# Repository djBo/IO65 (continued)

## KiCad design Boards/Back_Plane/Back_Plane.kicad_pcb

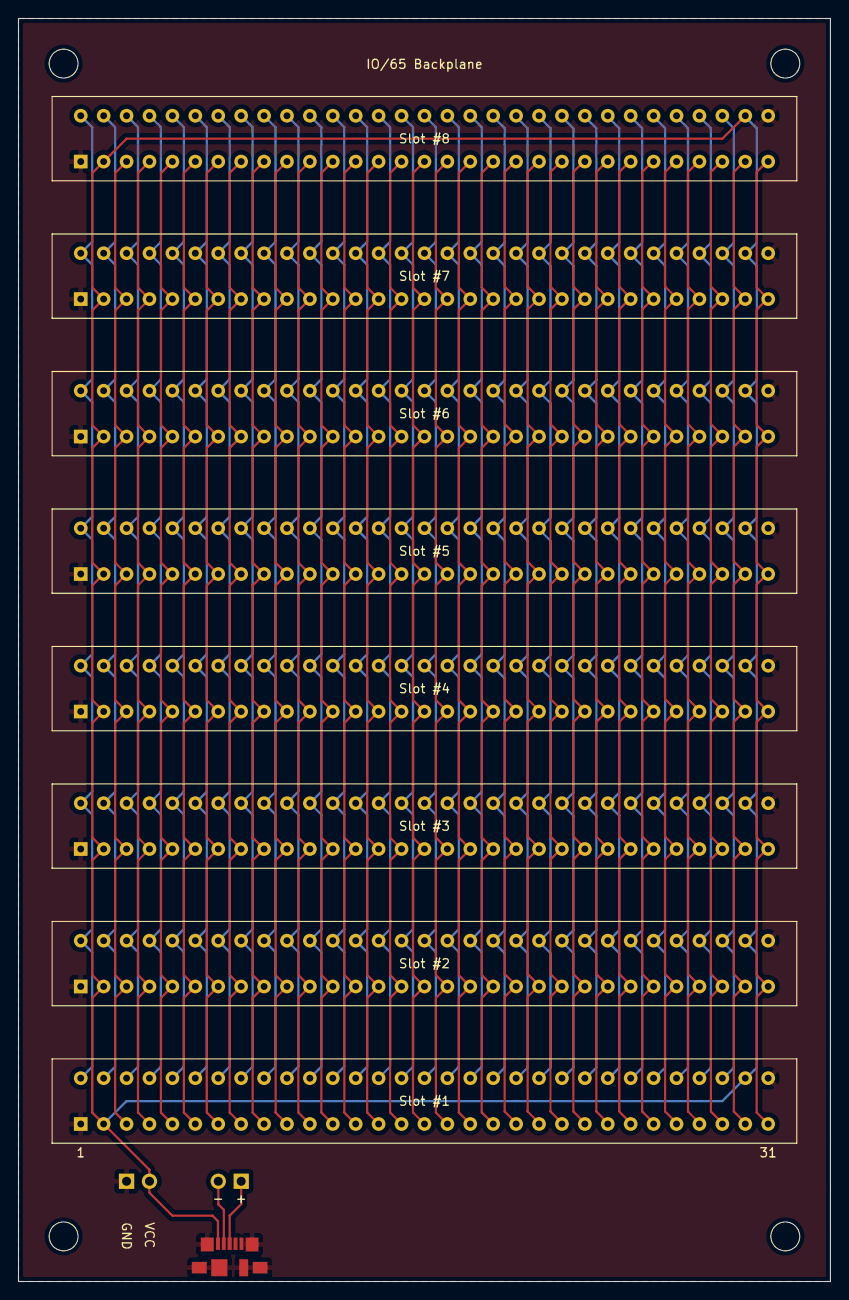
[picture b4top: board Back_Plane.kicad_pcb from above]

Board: 2 copper layers, 90.0 x 140.0 mm, 11 parts (0 on the bottom side), 62 nets.

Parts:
DATA1: Conn_01x02_Male; PinHeader_1x02_P2.54mm_Vertical
PWR1: Conn_01x02_Male; PinHeader_1x02_P2.54mm_Horizontal
Slot #1, Slot #2, Slot #3, Slot #4, Slot #5, Slot #6, Slot #7, Slot #8: Edge Connector; 6-5530843-5
USB1: USB_B_Micro; USB_Micro-B_Molex_47346-0001

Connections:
A0: Slot #1.47, Slot #2.47, Slot #3.47, Slot #4.47, Slot #5.47, Slot #6.47, Slot #7.47, Slot #8.47
A1: Slot #1.46, Slot #2.46, Slot #3.46, Slot #4.46, Slot #5.46, Slot #6.46, Slot #7.46, Slot #8.46
A2: Slot #1.45, Slot #2.45, Slot #3.45, Slot #4.45, Slot #5.45, Slot #6.45, Slot #7.45, Slot #8.45
A3: Slot #1.44, Slot #2.44, Slot #3.44, Slot #4.44, Slot #5.44, Slot #6.44, Slot #7.44, Slot #8.44
A4: Slot #1.43, Slot #2.43, Slot #3.43, Slot #4.43, Slot #5.43, Slot #6.43, Slot #7.43, Slot #8.43
A5: Slot #1.42, Slot #2.42, Slot #3.42, Slot #4.42, Slot #5.42, Slot #6.42, Slot #7.42, Slot #8.42
A6: Slot #1.41, Slot #2.41, Slot #3.41, Slot #4.41, Slot #5.41, Slot #6.41, Slot #7.41, Slot #8.41
A7: Slot #1.40, Slot #2.40, Slot #3.40, Slot #4.40, Slot #5.40, Slot #6.40, Slot #7.40, Slot #8.40
A8: Slot #1.39, Slot #2.39, Slot #3.39, Slot #4.39, Slot #5.39, Slot #6.39, Slot #7.39, Slot #8.39
A9: Slot #1.38, Slot #2.38, Slot #3.38, Slot #4.38, Slot #5.38, Slot #6.38, Slot #7.38, Slot #8.38
A10: Slot #1.37, Slot #2.37, Slot #3.37, Slot #4.37, Slot #5.37, Slot #6.37, Slot #7.37, Slot #8.37
A11: Slot #1.36, Slot #2.36, Slot #3.36, Slot #4.36, Slot #5.36, Slot #6.36, Slot #7.36, Slot #8.36
A12: Slot #1.35, Slot #2.35, Slot #3.35, Slot #4.35, Slot #5.35, Slot #6.35, Slot #7.35, Slot #8.35
A13: Slot #1.34, Slot #2.34, Slot #3.34, Slot #4.34, Slot #5.34, Slot #6.34, Slot #7.34, Slot #8.34
A14: Slot #1.33, Slot #2.33, Slot #3.33, Slot #4.33, Slot #5.33, Slot #6.33, Slot #7.33, Slot #8.33
A15: Slot #1.32, Slot #2.32, Slot #3.32, Slot #4.32, Slot #5.32, Slot #6.32, Slot #7.32, Slot #8.32
CA1: Slot #1.60, Slot #2.60, Slot #3.60, Slot #4.60, Slot #5.60, Slot #6.60, Slot #7.60, Slot #8.60
CA2: Slot #1.59, Slot #2.59, Slot #3.59, Slot #4.59, Slot #5.59, Slot #6.59, Slot #7.59, Slot #8.59
CS0: Slot #1.22, Slot #2.22, Slot #3.22, Slot #4.22, Slot #5.22, Slot #6.22, Slot #7.22, Slot #8.22
CS1: Slot #1.23, Slot #2.23, Slot #3.23, Slot #4.23, Slot #5.23, Slot #6.23, Slot #7.23, Slot #8.23
CS2: Slot #1.24, Slot #2.24, Slot #3.24, Slot #4.24, Slot #5.24, Slot #6.24, Slot #7.24, Slot #8.24
CS3: Slot #1.25, Slot #2.25, Slot #3.25, Slot #4.25, Slot #5.25, Slot #6.25, Slot #7.25, Slot #8.25
CS4: Slot #1.26, Slot #2.26, Slot #3.26, Slot #4.26, Slot #5.26, Slot #6.26, Slot #7.26, Slot #8.26
CS5: Slot #1.27, Slot #2.27, Slot #3.27, Slot #4.27, Slot #5.27, Slot #6.27, Slot #7.27, Slot #8.27
CS6: Slot #1.28, Slot #2.28, Slot #3.28, Slot #4.28, Slot #5.28, Slot #6.28, Slot #7.28, Slot #8.28
CS7: Slot #1.29, Slot #2.29, Slot #3.29, Slot #4.29, Slot #5.29, Slot #6.29, Slot #7.29, Slot #8.29
CS8: Slot #1.30, Slot #2.30, Slot #3.30, Slot #4.30, Slot #5.30, Slot #6.30, Slot #7.30, Slot #8.30
CS9: Slot #1.31, Slot #2.31, Slot #3.31, Slot #4.31, Slot #5.31, Slot #6.31, Slot #7.31, Slot #8.31
D0: Slot #1.9, Slot #2.9, Slot #3.9, Slot #4.9, Slot #5.9, Slot #6.9, Slot #7.9, Slot #8.9
D1: Slot #1.10, Slot #2.10, Slot #3.10, Slot #4.10, Slot #5.10, Slot #6.10, Slot #7.10, Slot #8.10
D2: Slot #1.11, Slot #2.11, Slot #3.11, Slot #4.11, Slot #5.11, Slot #6.11, Slot #7.11, Slot #8.11
D3: Slot #1.12, Slot #2.12, Slot #3.12, Slot #4.12, Slot #5.12, Slot #6.12, Slot #7.12, Slot #8.12
D4: Slot #1.13, Slot #2.13, Slot #3.13, Slot #4.13, Slot #5.13, Slot #6.13, Slot #7.13, Slot #8.13
D5: Slot #1.14, Slot #2.14, Slot #3.14, Slot #4.14, Slot #5.14, Slot #6.14, Slot #7.14, Slot #8.14
D6: Slot #1.15, Slot #2.15, Slot #3.15, Slot #4.15, Slot #5.15, Slot #6.15, Slot #7.15, Slot #8.15
D7: Slot #1.16, Slot #2.16, Slot #3.16, Slot #4.16, Slot #5.16, Slot #6.16, Slot #7.16, Slot #8.16
E1: Slot #1.17, Slot #2.17, Slot #3.17, Slot #4.17, Slot #5.17, Slot #6.17, Slot #7.17, Slot #8.17
E2: Slot #1.48, Slot #2.48, Slot #3.48, Slot #4.48, Slot #5.48, Slot #6.48, Slot #7.48, Slot #8.48
GND: PWR1.1, Slot #1.1, Slot #1.62, Slot #2.1, Slot #2.62, Slot #3.1, Slot #3.62, Slot #4.1, Slot #4.62, Slot #5.1, Slot #5.62, Slot #6.1, Slot #6.62, Slot #7.1, Slot #7.62, Slot #8.1, Slot #8.62, USB1.5 (GND), USB1.6 (Shield)
unnamed: DATA1.1, USB1.3 (D+)
unnamed: DATA1.2, USB1.2 (D-)
PA0: Slot #1.58, Slot #2.58, Slot #3.58, Slot #4.58, Slot #5.58, Slot #6.58, Slot #7.58, Slot #8.58
PA1: Slot #1.57, Slot #2.57, Slot #3.57, Slot #4.57, Slot #5.57, Slot #6.57, Slot #7.57, Slot #8.57
PA2: Slot #1.56, Slot #2.56, Slot #3.56, Slot #4.56, Slot #5.56, Slot #6.56, Slot #7.56, Slot #8.56
PA3: Slot #1.55, Slot #2.55, Slot #3.55, Slot #4.55, Slot #5.55, Slot #6.55, Slot #7.55, Slot #8.55
PA4: Slot #1.54, Slot #2.54, Slot #3.54, Slot #4.54, Slot #5.54, Slot #6.54, Slot #7.54, Slot #8.54
PA5: Slot #1.53, Slot #2.53, Slot #3.53, Slot #4.53, Slot #5.53, Slot #6.53, Slot #7.53, Slot #8.53
PA6: Slot #1.52, Slot #2.52, Slot #3.52, Slot #4.52, Slot #5.52, Slot #6.52, Slot #7.52, Slot #8.52
PA7: Slot #1.51, Slot #2.51, Slot #3.51, Slot #4.51, Slot #5.51, Slot #6.51, Slot #7.51, Slot #8.51
RAM: Slot #1.20, Slot #2.20, Slot #3.20, Slot #4.20, Slot #5.20, Slot #6.20, Slot #7.20, Slot #8.20
RDY: Slot #1.6, Slot #2.6, Slot #3.6, Slot #4.6, Slot #5.6, Slot #6.6, Slot #7.6, Slot #8.6
ROM: Slot #1.21, Slot #2.21, Slot #3.21, Slot #4.21, Slot #5.21, Slot #6.21, Slot #7.21, Slot #8.21
R/~W: Slot #1.4, Slot #2.4, Slot #3.4, Slot #4.4, Slot #5.4, Slot #6.4, Slot #7.4, Slot #8.4
SYNC: Slot #1.49, Slot #2.49, Slot #3.49, Slot #4.49, Slot #5.49, Slot #6.49, Slot #7.49, Slot #8.49
VCC: PWR1.2, Slot #1.2, Slot #1.61, Slot #2.2, Slot #2.61, Slot #3.2, Slot #3.61, Slot #4.2, Slot #4.61, Slot #5.2, Slot #5.61, Slot #6.2, Slot #6.61, Slot #7.2, Slot #7.61, Slot #8.2, Slot #8.61, USB1.1 (VBUS)
~IRQ: Slot #1.7, Slot #2.7, Slot #3.7, Slot #4.7, Slot #5.7, Slot #6.7, Slot #7.7, Slot #8.7
~NMI: Slot #1.8, Slot #2.8, Slot #3.8, Slot #4.8, Slot #5.8, Slot #6.8, Slot #7.8, Slot #8.8
~OE: Slot #1.18, Slot #2.18, Slot #3.18, Slot #4.18, Slot #5.18, Slot #6.18, Slot #7.18, Slot #8.18
~RES: Slot #1.5, Slot #2.5, Slot #3.5, Slot #4.5, Slot #5.5, Slot #6.5, Slot #7.5, Slot #8.5
~SO: Slot #1.50, Slot #2.50, Slot #3.50, Slot #4.50, Slot #5.50, Slot #6.50, Slot #7.50, Slot #8.50
~WE: Slot #1.19, Slot #2.19, Slot #3.19, Slot #4.19, Slot #5.19, Slot #6.19, Slot #7.19, Slot #8.19
Φ2: Slot #1.3, Slot #2.3, Slot #3.3, Slot #4.3, Slot #5.3, Slot #6.3, Slot #7.3, Slot #8.3

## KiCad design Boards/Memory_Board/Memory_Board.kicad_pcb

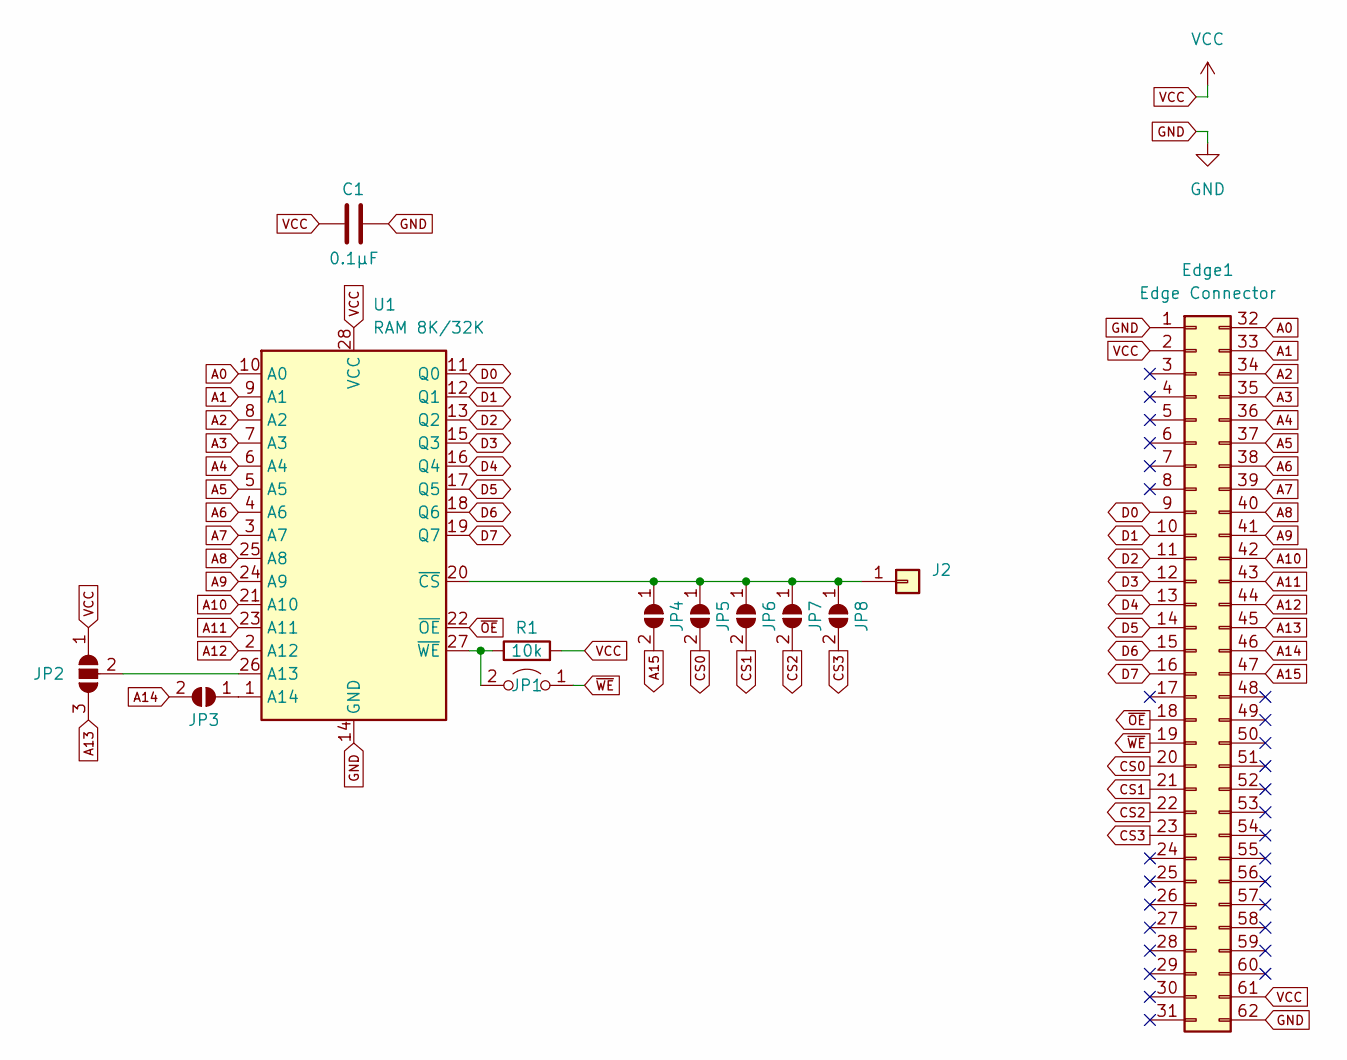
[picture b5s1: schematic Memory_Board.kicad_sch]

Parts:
C1: 0.1µF; C_Disc_D5.0mm_W2.5mm_P2.50mm
Edge1: Edge Connector; BUS_PC_M
J2: Conn_01x01; PinSocket_1x01_P2.54mm_Horizontal
JP1: Jumper_2_Open; PinHeader_1x02_P2.54mm_Horizontal
JP2: SolderJumper_3_Open; SolderJumper-3_P1.3mm_Open_Pad1.0x1.5mm
JP3, JP4, JP5, JP6, JP7, JP8: SolderJumper_2_Open; SolderJumper-2_P1.3mm_Open_Pad1.0x1.5mm
R1: 10k; R_Axial_DIN0207_L6.3mm_D2.5mm_P7.62mm_Horizontal
U1: RAM 8K/32K; DIP-28_W15.24mm_Socket

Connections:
A0: Edge1.32, U1.10 (A0)
A1: Edge1.33, U1.9 (A1)
A2: Edge1.34, U1.8 (A2)
A3: Edge1.35, U1.7 (A3)
A4: Edge1.36, U1.6 (A4)
A5: Edge1.37, U1.5 (A5)
A6: Edge1.38, U1.4 (A6)
A7: Edge1.39, U1.3 (A7)
A8: Edge1.40, U1.25 (A8)
A9: Edge1.41, U1.24 (A9)
A10: Edge1.42, U1.21 (A10)
A11: Edge1.43, U1.23 (A11)
A12: Edge1.44, U1.2 (A12)
A13: Edge1.45, JP2.3 (B)
A14: Edge1.46, JP3.2 (B)
A15: Edge1.47, JP4.2 (B)
CS0: Edge1.20, JP5.2 (B)
CS1: Edge1.21, JP6.2 (B)
CS2: Edge1.22, JP7.2 (B)
CS3: Edge1.23, JP8.2 (B)
D0: Edge1.9, U1.11 (Q0)
D1: Edge1.10, U1.12 (Q1)
D2: Edge1.11, U1.13 (Q2)
D3: Edge1.12, U1.15 (Q3)
D4: Edge1.13, U1.16 (Q4)
D5: Edge1.14, U1.17 (Q5)
D6: Edge1.15, U1.18 (Q6)
D7: Edge1.16, U1.19 (Q7)
GND: C1.2, Edge1.1, Edge1.62, U1.14 (GND)
unnamed: J2.1, JP4.1 (A), JP5.1 (A), JP6.1 (A), JP7.1 (A), JP8.1 (A), U1.20 (~CS)
unnamed 30: JP1.2 (B), R1.1, U1.27 (~WE); also elsewhere on the board
unnamed: JP2.2 (C), U1.26 (A13)
unnamed: JP3.1 (A), U1.1 (A14)
VCC: C1.1, Edge1.2, Edge1.61, JP2.1 (A), R1.2, U1.28 (VCC)
~OE: Edge1.18, U1.22 (~OE)
~WE: Edge1.19, JP1.1 (A); also elsewhere on the board

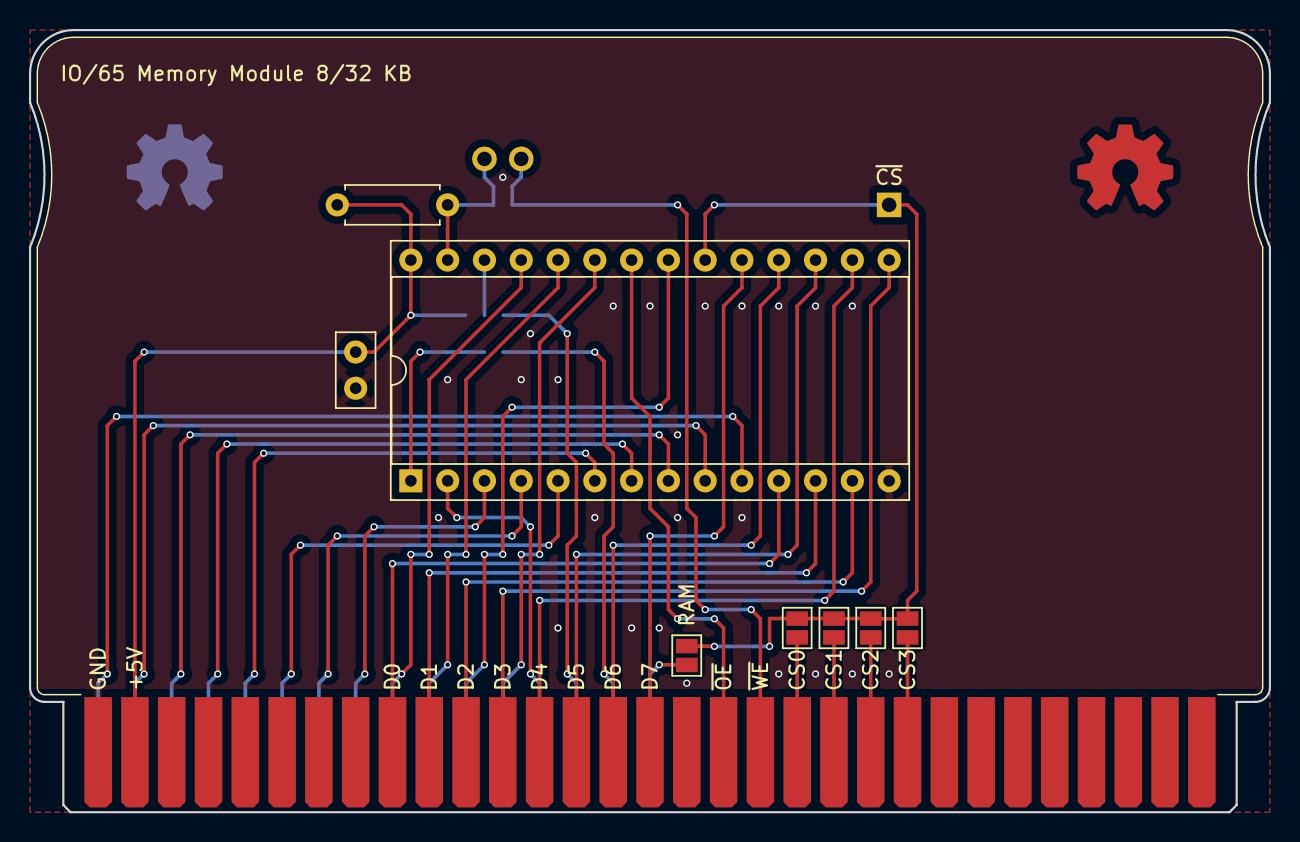
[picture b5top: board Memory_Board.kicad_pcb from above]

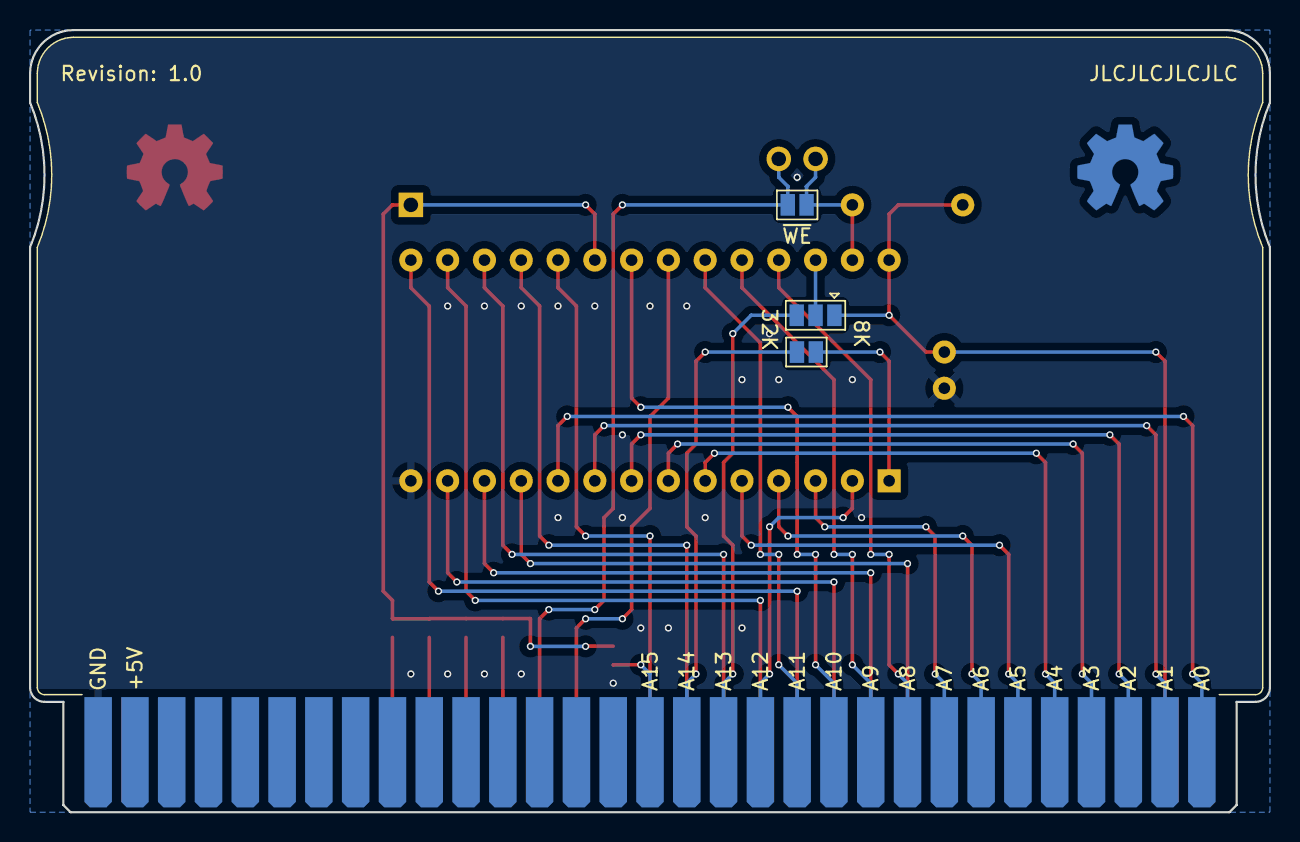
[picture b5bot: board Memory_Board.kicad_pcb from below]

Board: 2 copper layers, 85.6 x 54.0 mm, 18 parts (7 on the bottom side), 36 nets.

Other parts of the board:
JP1b: SolderJumper_2_Open; SolderJumper-2_P1.3mm_Open_Pad1.0x1.5mm
LogoBack: OSHW-Symbol_6.7x6mm_Copper
LogoBackMask: OSHW-Symbol_6.7x6mm_Copper
LogoFront: OSHW-Symbol_6.7x6mm_Copper
LogoFrontMask: OSHW-Symbol_6.7x6mm_Copper

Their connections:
unnamed 30: JP1b.2 (B); also elsewhere on the board
~WE: JP1b.1 (A); also elsewhere on the board

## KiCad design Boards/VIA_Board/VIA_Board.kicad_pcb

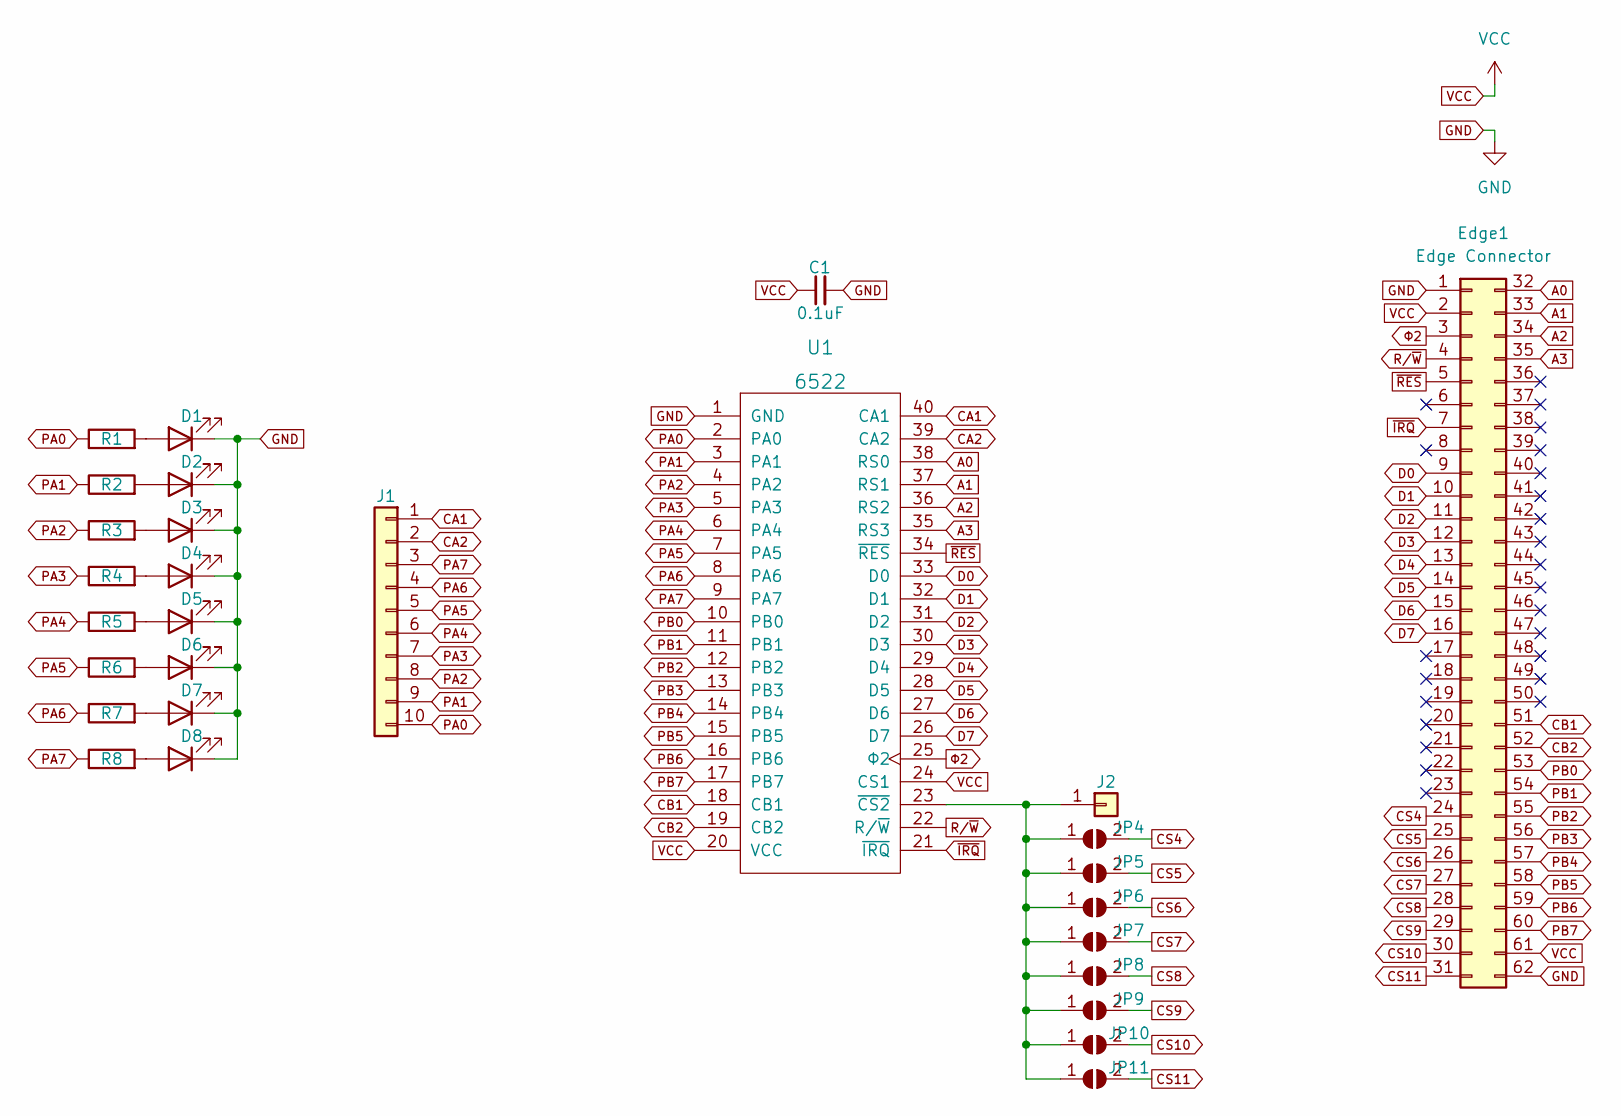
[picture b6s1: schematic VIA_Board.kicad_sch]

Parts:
C1: 0.1uF; C_Disc_D4.7mm_W2.5mm_P5.00mm
D1, D2, D3, D4, D5, D6, D7, D8: LED; LED_0603_1608Metric_Pad1.05x0.95mm_HandSolder
Edge1: Edge Connector; BUS_PC_M
J1: Conn_01x08; PinSocket_1x08_P2.54mm_Horizontal
J2: Conn_01x01; PinSocket_1x01_P2.54mm_Horizontal
JP4, JP5, JP6, JP7, JP8, JP9, JP10, JP11: SolderJumper_2_Open; SolderJumper-2_P1.3mm_Open_Pad1.0x1.5mm
R1, R2, R3, R4, R5, R6, R7, R8: R; R_0603_1608Metric_Pad0.98x0.95mm_HandSolder
U1: 6522; DIP-40_W15.24mm_Socket

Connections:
A0: Edge1.32, U1.38 (RS0)
A1: Edge1.33, U1.37 (RS1)
A2: Edge1.34, U1.36 (RS2)
A3: Edge1.35, U1.35 (RS3)
CA1: J1.1, U1.40 (CA1)
CA2: J1.2, U1.39 (CA2)
CB1: Edge1.51, U1.18 (CB1)
CB2: Edge1.52, U1.19 (CB2)
CS4: Edge1.24, JP4.2 (B)
CS5: Edge1.25, JP5.2 (B)
CS6: Edge1.26, JP6.2 (B)
CS7: Edge1.27, JP7.2 (B)
CS8: Edge1.28, JP8.2 (B)
CS9: Edge1.29, JP9.2 (B)
CS10: Edge1.30, JP10.2 (B)
CS11: Edge1.31, JP11.2 (B)
D0: Edge1.9, U1.33 (D0)
D1: Edge1.10, U1.32 (D1)
D2: Edge1.11, U1.31 (D2)
D3: Edge1.12, U1.30 (D3)
D4: Edge1.13, U1.29 (D4)
D5: Edge1.14, U1.28 (D5)
D6: Edge1.15, U1.27 (D6)
D7: Edge1.16, U1.26 (D7)
GND: C1.2, D1.1 (K), D2.1 (K), D3.1 (K), D4.1 (K), D5.1 (K), D6.1 (K), D7.1 (K), D8.1 (K), Edge1.1, Edge1.62, U1.1 (GND)
unnamed: D1.2 (A), R1.2
unnamed: D2.2 (A), R2.2
unnamed: D3.2 (A), R3.2
unnamed: D4.2 (A), R4.2
unnamed: D5.2 (A), R5.2
unnamed: D6.2 (A), R6.2
unnamed: D7.2 (A), R7.2
unnamed: D8.2 (A), R8.2
unnamed: J2.1, JP4.1 (A), JP5.1 (A), JP6.1 (A), JP7.1 (A), JP8.1 (A), JP9.1 (A), JP10.1 (A), JP11.1 (A), U1.23 (~CS2)
PA0: J1.10, R1.1, U1.2 (PA0)
PA1: J1.9, R2.1, U1.3 (PA1)
PA2: J1.8, R3.1, U1.4 (PA2)
PA3: J1.7, R4.1, U1.5 (PA3)
PA4: J1.6, R5.1, U1.6 (PA4)
PA5: J1.5, R6.1, U1.7 (PA5)
PA6: J1.4, R7.1, U1.8 (PA6)
PA7: J1.3, R8.1, U1.9 (PA7)
PB0: Edge1.53, U1.10 (PB0)
PB1: Edge1.54, U1.11 (PB1)
PB2: Edge1.55, U1.12 (PB2)
PB3: Edge1.56, U1.13 (PB3)
PB4: Edge1.57, U1.14 (PB4)
PB5: Edge1.58, U1.15 (PB5)
PB6: Edge1.59, U1.16 (PB6)
PB7: Edge1.60, U1.17 (PB7)
R/~W: Edge1.4, U1.22 (R/~W)
VCC: C1.1, Edge1.2, Edge1.61, U1.20 (VCC), U1.24 (CS1)
~IRQ: Edge1.7, U1.21 (~IRQ)
~RES: Edge1.5, U1.34 (~RES)
Φ2: Edge1.3, U1.25 (Φ2)

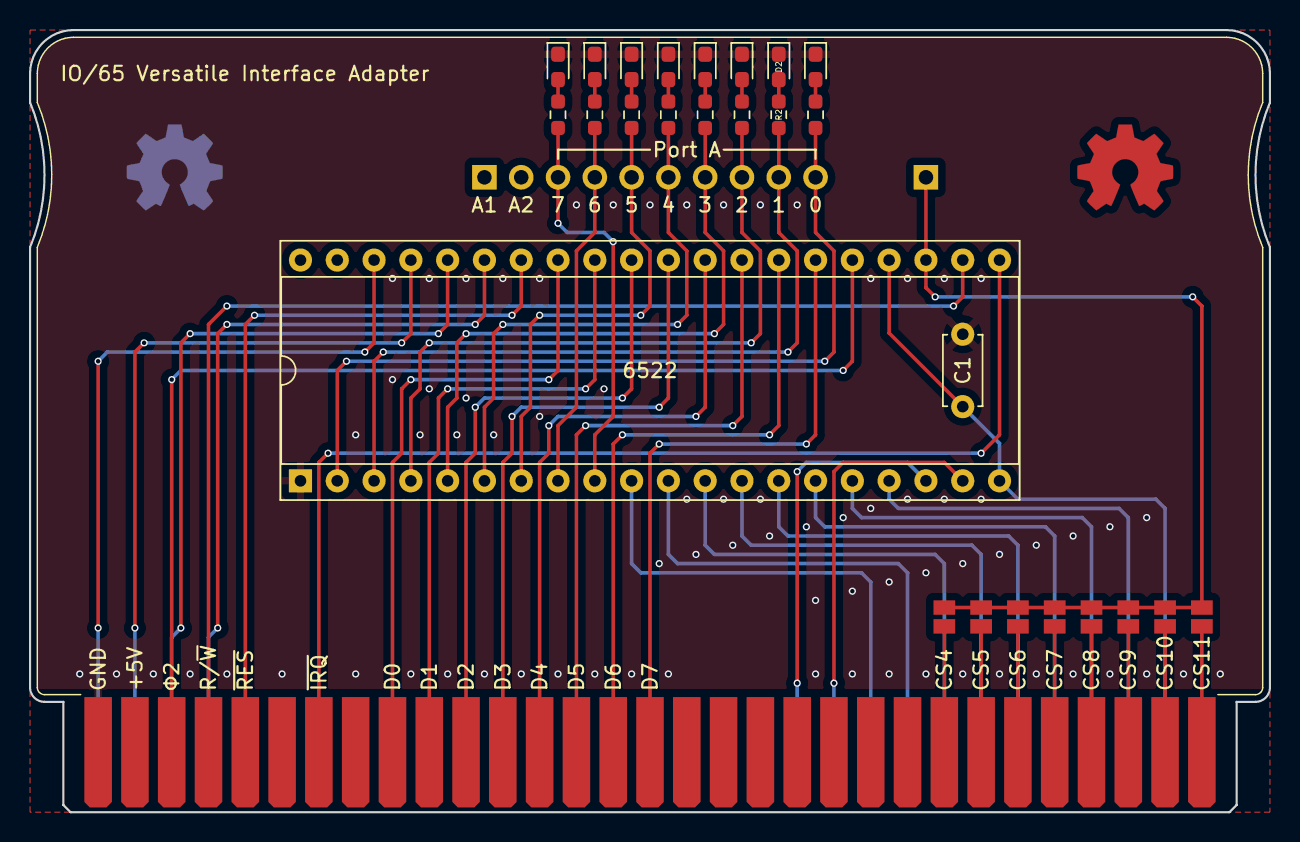
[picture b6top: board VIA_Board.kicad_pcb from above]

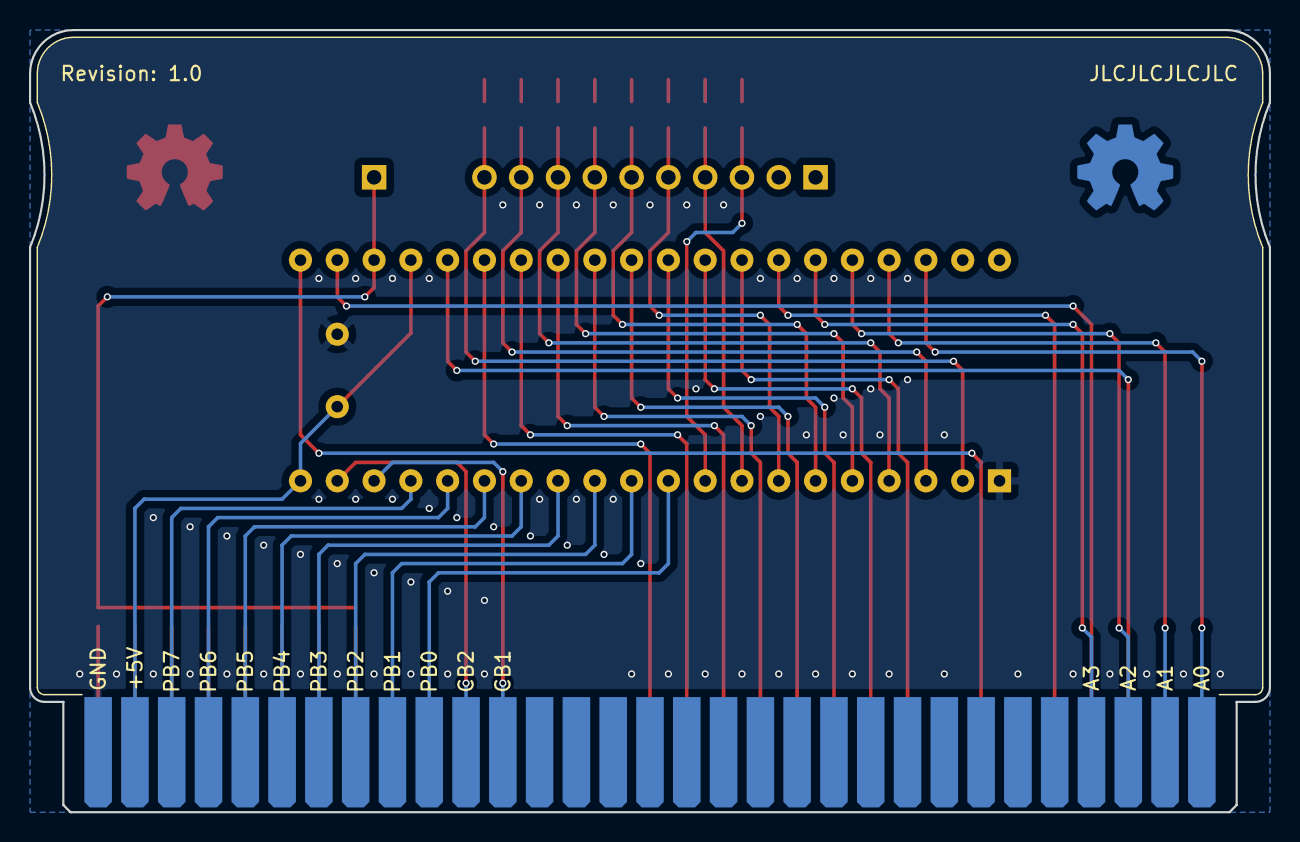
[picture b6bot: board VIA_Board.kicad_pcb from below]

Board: 2 copper layers, 85.6 x 54.0 mm, 33 parts (4 on the bottom side), 55 nets.

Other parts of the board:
LogoBack: OSHW-Symbol_6.7x6mm_Copper
LogoBackMask: OSHW-Symbol_6.7x6mm_Copper
LogoFront: OSHW-Symbol_6.7x6mm_Copper
LogoFrontMask: OSHW-Symbol_6.7x6mm_Copper

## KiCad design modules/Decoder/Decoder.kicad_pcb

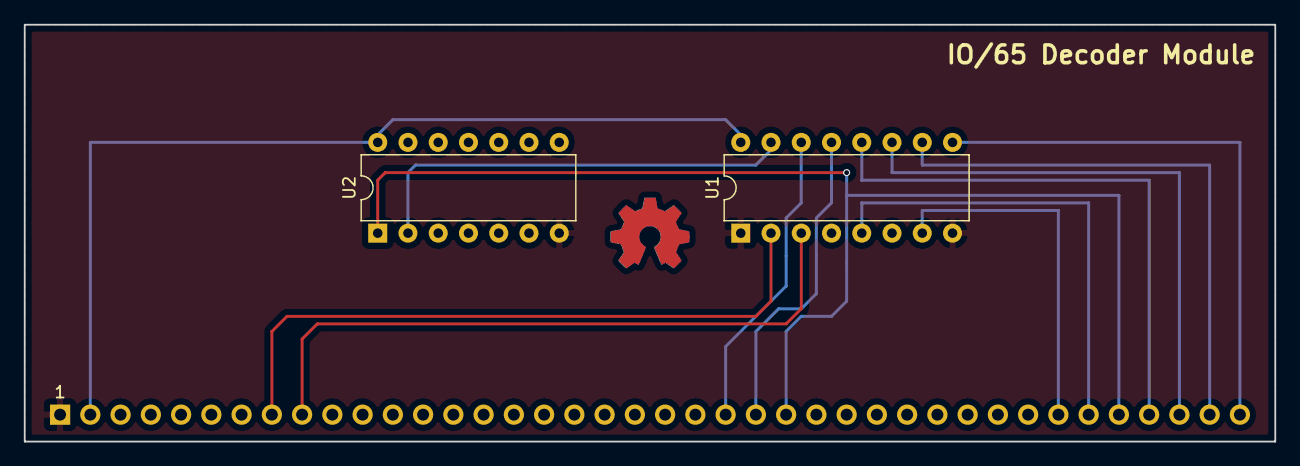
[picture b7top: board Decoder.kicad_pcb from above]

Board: 2 copper layers, 105.0 x 35.0 mm, 3 parts (1 on the bottom side), 14 nets.

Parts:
J1: Header; Pin_Header_Angled_1x40_Pitch2.54mm
U1: 74LS139; DIP-16_W7.62mm
U2: 74LS04; DIP-14_W7.62mm

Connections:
A13: J1.23, U1.14
A14: J1.24, U1.13
A15: J1.25, J1.36, U2.1
CS_8000-9FFF: J1.37, U1.12
CS_A000-BFFF: J1.38, U1.11
CS_C000-DFFF: J1.39, U1.10
CS_E000-FFFF: J1.40, U1.9
GND: J1.1, U1.1, U1.8, U2.7
unnamed: U1.15, U2.2
OE: J1.34, U1.7
R/~W: J1.9, U1.3
VCC: J1.2, U1.16, U2.14
WE: J1.35, U1.5
Φ2: J1.8, U1.2

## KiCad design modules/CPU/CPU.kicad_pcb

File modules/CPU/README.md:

## IO/65 CPU Module
This module represents the start of the project and the main component of the platform. It consists of a simple board exposing the buses and control lines. It allows free-running of the CPU when powered standalone.

Features:

- Unbuffered access to address and databus
- Pull-down resistors on the data bus to allow free-running
- Pull-up resistors on the control lines
- Switching between internal and external clock
- Reset button

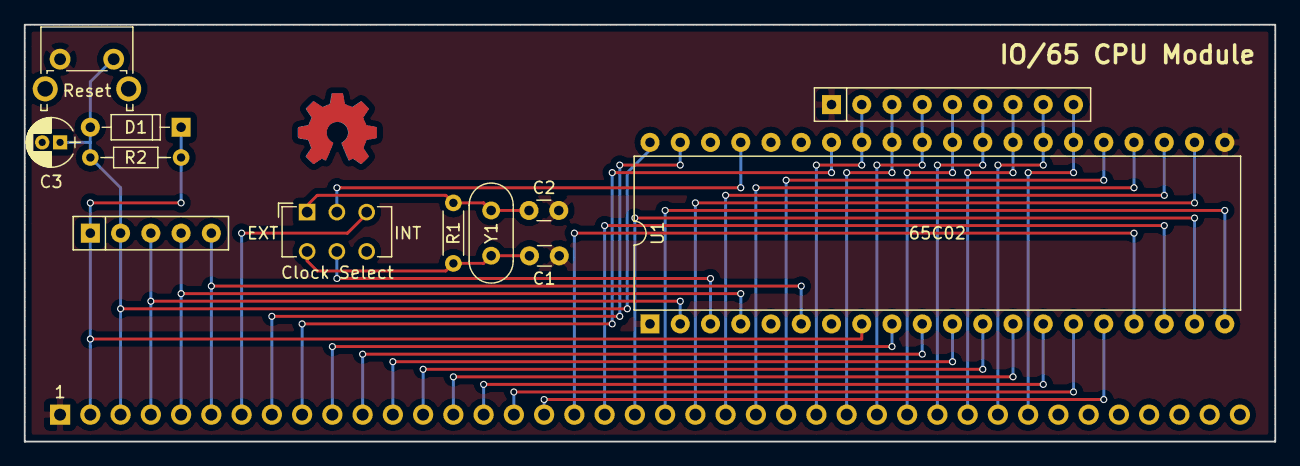
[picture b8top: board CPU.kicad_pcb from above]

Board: 2 copper layers, 105.0 x 35.0 mm, 13 parts (1 on the bottom side), 37 nets.

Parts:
C1, C2: 47pF; C_Disc_D3.0mm_W1.6mm_P2.50mm
C3: 10μF; CP_Radial_D4.0mm_P1.50mm
D1: 1N4148; D_DO-35_SOD27_P7.62mm_Horizontal
J1: Header; Pin_Header_Angled_1x40_Pitch2.54mm
R1: 100k; R_Axial_DIN0204_L3.6mm_D1.6mm_P5.08mm_Horizontal
R2: 4k7; R_Axial_DIN0204_L3.6mm_D1.6mm_P7.62mm_Horizontal
RN1: 4k7; R_Array_SIP5
RN2: 4k7; R_Array_SIP9
SW1: Clock Select; SW_CuK_JS202011CQN_DPDT_Straight
SW2: Reset; SW_Tactile_SPST_Angled_PTS645Vx39-2LFS
U1: 65C02; DIP-40_W15.24mm
Y1: 1MHz; Crystal_HC52-6mm_Vertical

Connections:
A0: J1.10, U1.9
A1: J1.11, U1.10
A2: J1.12, U1.11
A3: J1.13, U1.12
A4: J1.14, U1.13
A5: J1.15, U1.14
A6: J1.16, U1.15
A7: J1.17, U1.16
A8: J1.18, U1.17
A9: J1.19, U1.18
A10: J1.20, U1.19
A11: J1.21, U1.20
A12: J1.22, U1.22
A13: J1.23, U1.23
A14: J1.24, U1.24
A15: J1.25, U1.25
CLK: J1.7, SW1.3
D0: J1.26, RN2.2, U1.33
D1: J1.27, RN2.3, U1.32
D2: J1.28, RN2.4, U1.31
D3: J1.29, RN2.5, U1.30
D4: J1.30, RN2.6, U1.29
D5: J1.31, RN2.7, U1.28
D6: J1.32, RN2.8, U1.27
D7: J1.33, RN2.9, U1.26
GND: C1.1, C2.2, C3.2, J1.1, RN2.1, SW2.1, U1.1, U1.21
IRQ: J1.5, RN1.4, U1.4
NMI: J1.6, RN1.5, U1.6
unnamed: C1.2, R1.1, SW1.4, Y1.2
unnamed: C2.1, R1.2, SW1.1, Y1.1
R/W: J1.9, U1.34
RDY: J1.4, RN1.3, U1.2
RES: C3.1, D1.2, J1.3, R2.2, RN1.2, SW2.2, U1.40
VCC: D1.1, J1.2, R2.1, RN1.1, U1.8
Φ0: SW1.2, U1.37
Φ1: SW1.5, U1.3
Φ2: J1.8, U1.39

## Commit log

2017-11-10 Adding the CPU module designs
2017-11-15 Adding the decoder module designs
2023-06-02 Adding boards as ordered from JLCPCB
2023-06-07 Rename+.gitignore
2024-03-09 Fixed bugs in CPU module, adding an inverter to the 555 timer output and properly routing it's VCC Fixed bug in Address Decoder, fixing the wiring of the enable inputs Updated Readme.md, and added Di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
